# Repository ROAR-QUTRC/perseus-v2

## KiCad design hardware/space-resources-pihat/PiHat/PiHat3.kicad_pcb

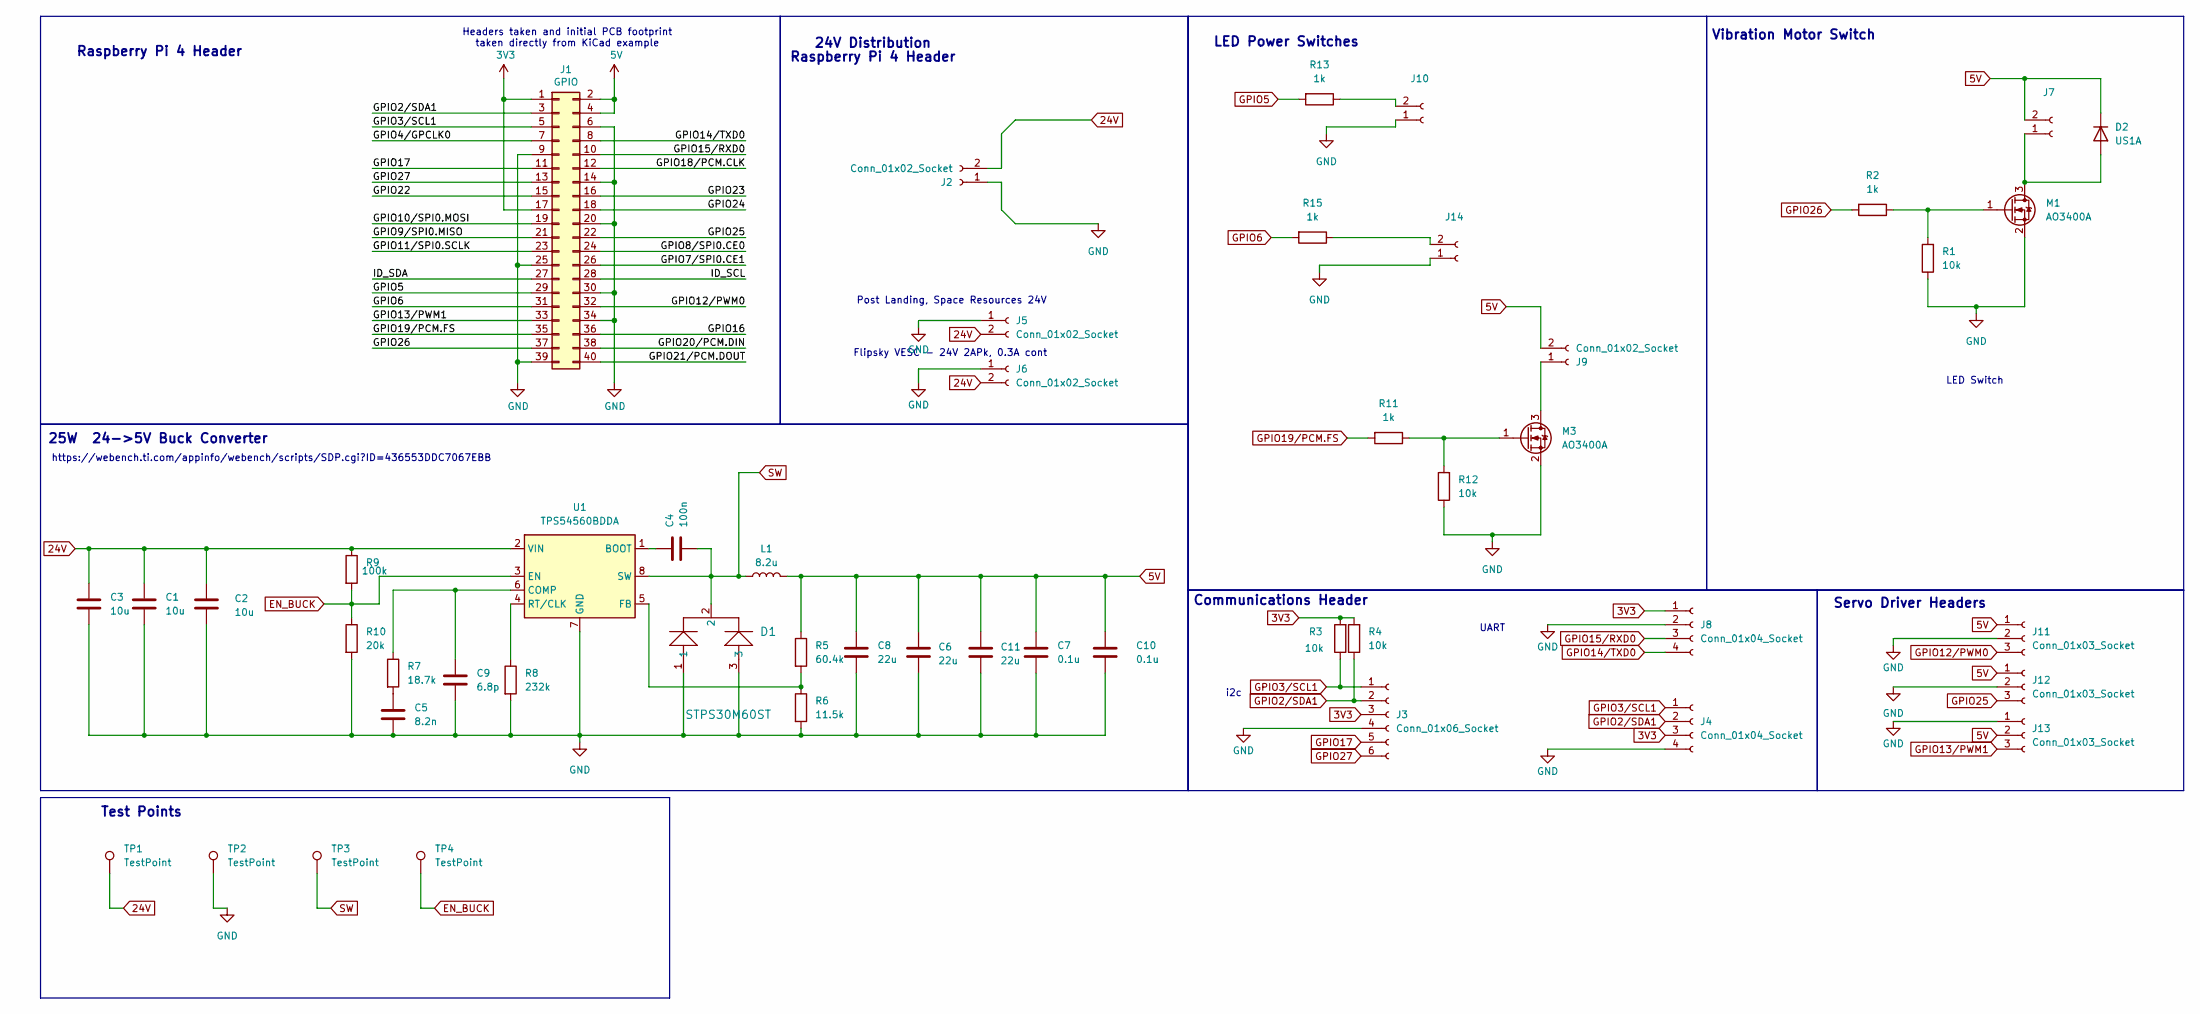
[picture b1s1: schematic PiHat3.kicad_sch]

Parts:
C1, C2, C3: 10u; C_1206_3216Metric_Pad1.33x1.80mm_HandSolder
C4: 100n; C_0603_1608Metric
C5: 8.2n; C_0603_1608Metric
C6, C8, C11: 22u; C_1210_3225Metric_Pad1.33x2.70mm_HandSolder
C7, C10: 0.1u; C_0603_1608Metric
C9: 6.8p; C_0603_1608Metric
D1: STPS30M60ST; TO-220AB_STM
D2: US1A; D_SMA
J1: GPIO; PinSocket_2x20_P2.54mm_Vertical
J2, J5, J6: Conn_01x02_Socket; AMASS_XT90PW-M_1x02_P10.90mm_Horizontal
J3: Conn_01x06_Socket; JST_EH_B6B-EH-A_1x06_P2.50mm_Vertical
J4, J8: Conn_01x04_Socket; JST_EH_B4B-EH-A_1x04_P2.50mm_Vertical
J7, J9, J10, J14: Conn_01x02_Socket; JST_EH_B2B-EH-A_1x02_P2.50mm_Vertical
J11, J12, J13: Conn_01x03_Socket; JST_EH_B3B-EH-A_1x03_P2.50mm_Vertical
L1: 8.2u; L_Bourns_SRR1210A
M1, M3: AO3400A; SOT-23
R1, R3, R4, R12: 10k; R_0603_1608Metric_Pad0.98x0.95mm_HandSolder
R2, R11, R13, R15: 1k; R_0603_1608Metric_Pad0.98x0.95mm_HandSolder
R5: 60.4k; R_0603_1608Metric_Pad0.98x0.95mm_HandSolder
R6: 11.5k; R_0603_1608Metric_Pad0.98x0.95mm_HandSolder
R7: 18.7k; R_0603_1608Metric_Pad0.98x0.95mm_HandSolder
R8: 232k; R_0603_1608Metric_Pad0.98x0.95mm_HandSolder
R9: 100k; R_0603_1608Metric_Pad0.98x0.95mm_HandSolder
R10: 20k; R_0603_1608Metric_Pad0.98x0.95mm_HandSolder
TP1, TP2, TP3, TP4: TestPoint; PinHeader_1x01_P1.00mm_Vertical
U1: TPS54560BDDA; Texas_R-PDSO-G8_EP2.95x4.9mm_Mask2.4x3.1mm_ThermalVias

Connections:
3V3: J1.1, J1.17, J3.3, J4.3, J8.1, R3.2, R4.2
5V: C6.1, C7.1, C8.1, C10.1, C11.1, D2.1 (K), J1.2, J1.4, J7.2, J9.2, J11.1, J12.1, J13.2, L1.2, R5.1; also elsewhere on the board
24V: C1.1, C2.1, C3.1, J2.2, J5.2, J6.2, R9.1, TP1.1, U1.2 (VIN)
/GPIO4/GPCLK0: J1.7
/GPIO7/SPI0.CE1: J1.26
/GPIO8/SPI0.CE0: J1.24
/GPIO9/SPI0.MISO: J1.21
/GPIO10/SPI0.MOSI: J1.19
/GPIO11/SPI0.SCLK: J1.23
/GPIO16: J1.36
/GPIO18/PCM.CLK: J1.12
/GPIO20/PCM.DIN: J1.38
/GPIO21/PCM.DOUT: J1.40
/GPIO22: J1.15
/GPIO23: J1.16
/GPIO24: J1.18
/ID_SCL: J1.28
/ID_SDA: J1.27
EN_BUCK: R9.2, R10.1, TP4.1, U1.3 (EN)
GND: C1.2, C2.2, C3.2, C5.2, C6.2, C7.2, C8.2, C9.2, C10.2, C11.2, D1.1, D1.3, J1.6, J1.9, J1.14, J1.20, J1.25, J1.30, J1.34, J1.39, J2.1, J3.4, J4.4, J5.1, J6.1, J8.2, J10.1, J11.2, J12.2, J13.1, J14.1, M1.2 (S), M3.2 (S), R1.1, R6.2, R8.2, R10.2, R12.1, TP2.1, U1.7 (GND), U1.9 (GND); also elsewhere on the board
GPIO2/SDA1: J1.3, J3.2, J4.2, R4.1
GPIO3/SCL1: J1.5, J3.1, J4.1, R3.1
GPIO5: J1.29, R13.2
GPIO6: J1.31, R15.2
GPIO12/PWM0: J1.32, J11.3
GPIO13/PWM1: J1.33, J13.3
GPIO14/TXD0: J1.8, J8.4
GPIO15/RXD0: J1.10, J8.3
GPIO17: J1.11, J3.5
GPIO19/PCM.FS: J1.35, R11.2
GPIO25: J1.22, J12.3
GPIO26: J1.37, R2.2
GPIO27: J1.13, J3.6
unnamed: C5.1, R7.2
unnamed: D2.2 (A), J7.1, M1.3 (D)
unnamed: J9.1, M3.3 (D)
unnamed: J10.2, R13.1
unnamed: J14.2, R15.1
unnamed: M1.1 (G), R1.2, R2.1
unnamed: M3.1 (G), R11.1, R12.2
unnamed: C4.1, U1.1 (BOOT)
unnamed: C9.1, R7.1, U1.6 (COMP)
unnamed: R5.2, R6.1, U1.5 (FB)
unnamed: R8.1, U1.4 (RT/CLK)
SW: C4.2, D1.2, L1.1, TP3.1, U1.8 (SW)

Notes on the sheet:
https://webench.ti.com/appinfo/webench/scripts/SDP.cgi?ID=436553DDC7067EBB
Servo Driver Headers
Headers taken and initial PCB footprint taken directly from KiCad example
Post Landing, Space Resources 24V
UART
Vibration Motor Switch
24V Distribution
Flipsky VESC - 24V 2APk, 0.3A cont
i2c
LED Power Switches
LED Switch
Raspberry Pi 4 Header
Test Points
25W 24->5V Buck Converter
Communications Header

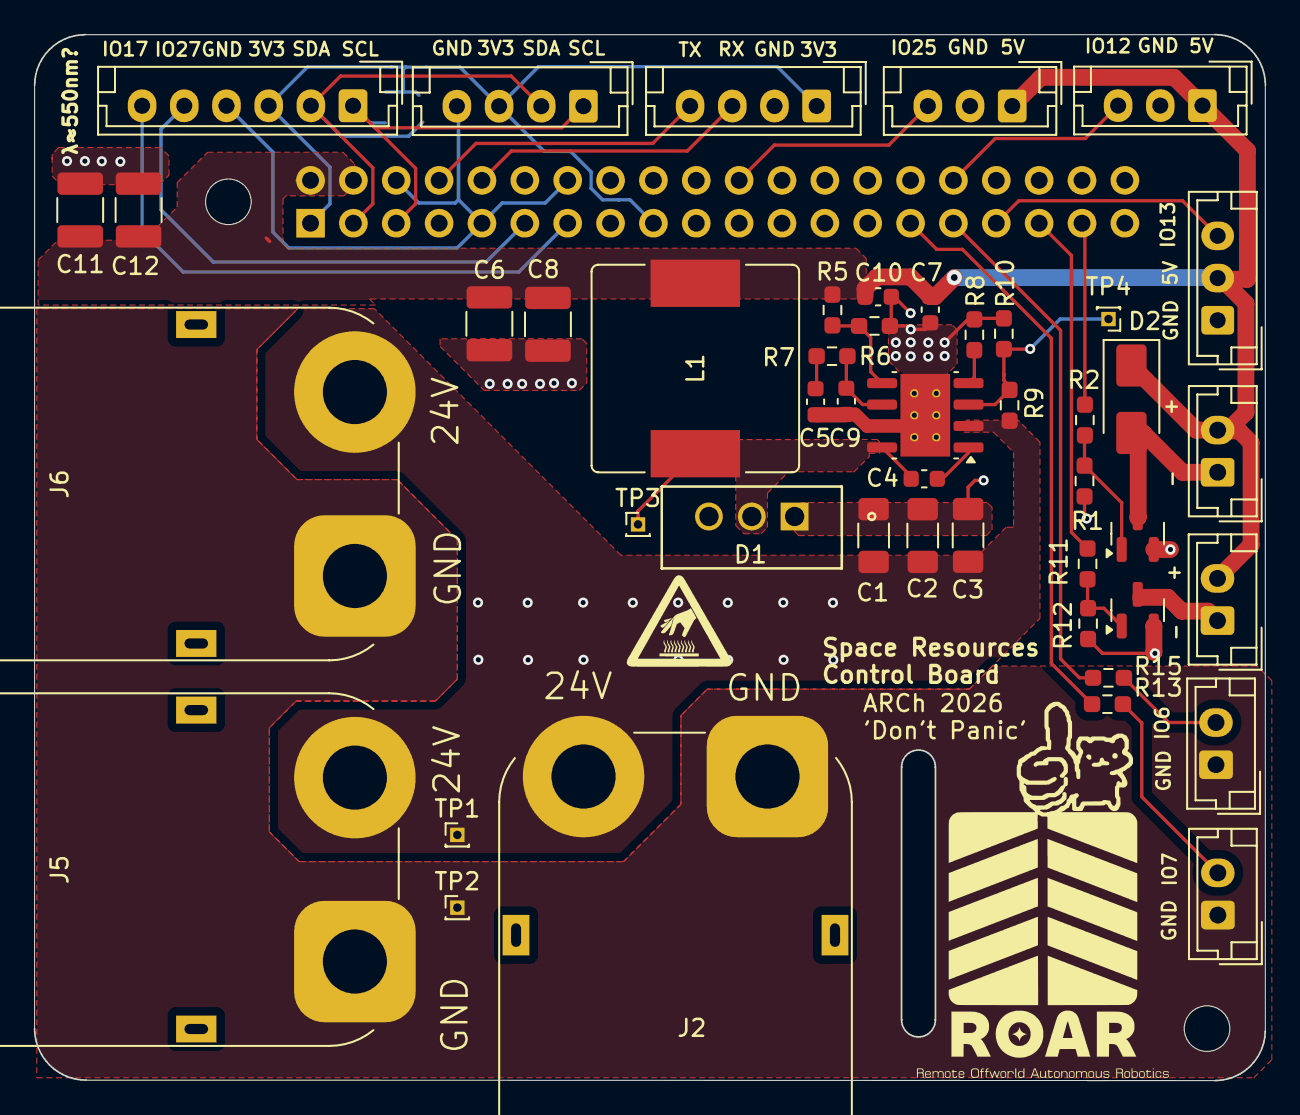
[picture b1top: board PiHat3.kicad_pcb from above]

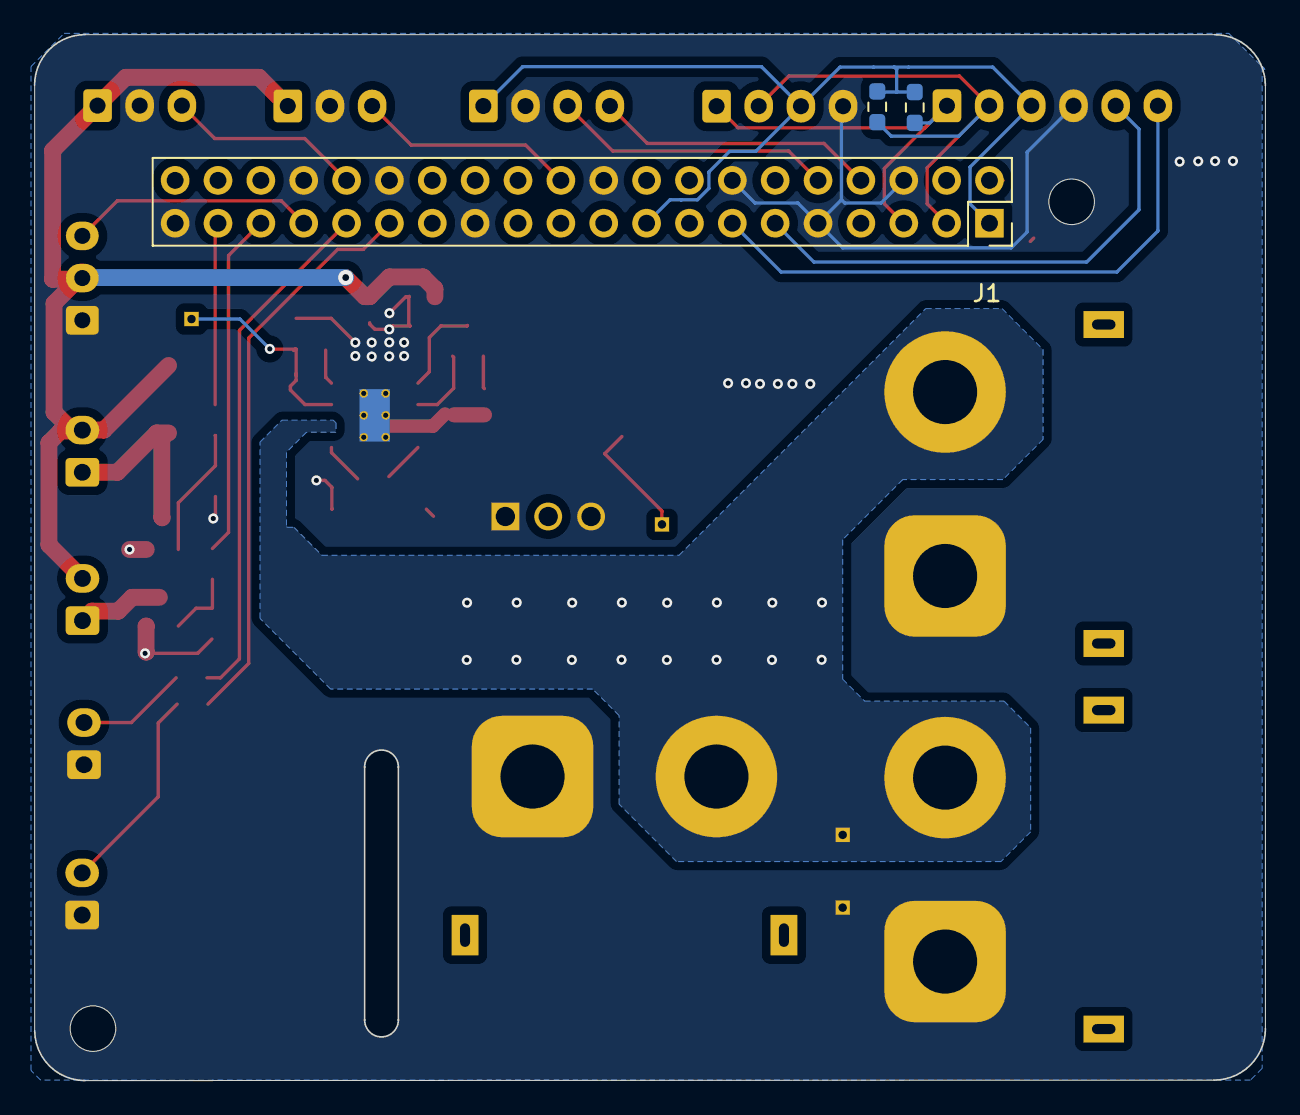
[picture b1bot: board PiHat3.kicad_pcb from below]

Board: 2 copper layers, 72.9 x 62.0 mm, 52 parts (3 on the bottom side), 30 nets.

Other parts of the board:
C12: 22u; C_1210_3225Metric_Pad1.33x2.70mm_HandSolder
MH1, MH4: MountingHole_2.7mm_M2.5

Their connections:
5V: C12.1; also elsewhere on the board
GND: C12.2; also elsewhere on the board
